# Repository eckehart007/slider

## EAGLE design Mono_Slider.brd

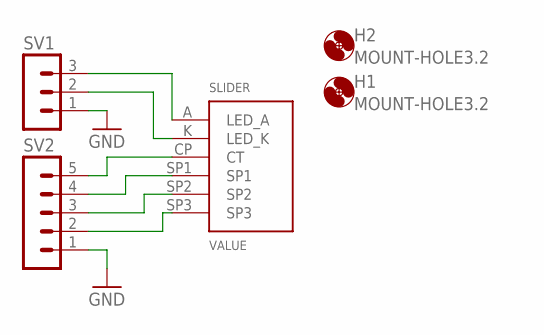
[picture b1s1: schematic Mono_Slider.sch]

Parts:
H1, H2: MOUNT-HOLE3.2; 3,2
SL1: SLIDER; SLIDER_SMALL
SV1: MA03-1
SV2: MA05-1

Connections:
A: SL1.A (LED_A), SV1.3
CP: SL1.CP (CT), SV2.5
GND: SV1.1, SV2.1
K: SL1.K (LED_K), SV1.2
SP1: SL1.SP1, SV2.4
SP2: SL1.SP2, SV2.3
SP3: SL1.SP3, SV2.2

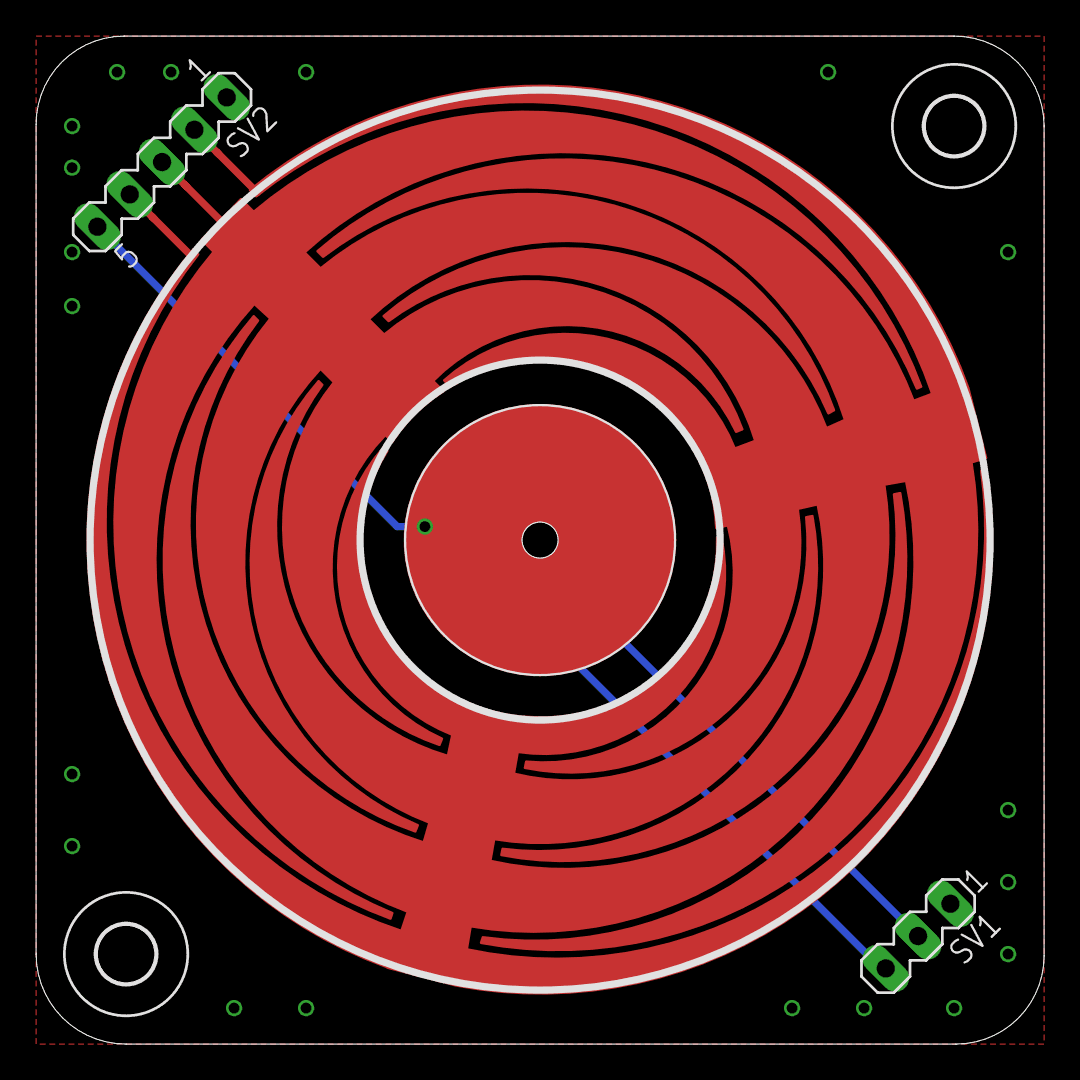
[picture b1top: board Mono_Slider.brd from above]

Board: 2 copper layers, 56.0 x 56.0 mm, 5 parts (0 on the bottom side), 7 nets.

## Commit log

2017-01-29 init
2017-03-26 Made slider smaller.
2017-03-27 Made pcb smaller to fit in case..
2017-03-27 Made round corners and added need gnd pours. TODO Check hatch size, stitching vias, names for pins, version.
2017-03-28 Changed hatch, silk and clearence
2017-03-30 Final, Led is not component??, Bom headers are not selected..
2017-10-15 Uncommited changes
2017-11-04 tühi
2017-11-04 Gerbers
